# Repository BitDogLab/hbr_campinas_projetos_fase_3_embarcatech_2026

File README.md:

# EmbarcaTech 2026

## Repositório de Segurança - Projetos Finais da Fase 3

Este repositório contém cópias dos Projetos Finais dos alunos da 3ª Fase do Curso Embarcatech (1ª Edição, realizada de 10/2025 a 02/2025).

## Professores e Monitores
- Prof. Fabiano Fruett
- Prof. Lorenzo Coiado
- Rafael Camargo de Magalhães
- Timóteo Altoé Bento da Silva
- Vinícius Emanoel Ares

## Grupos

### G1 - Controle de Acesso
- Adriana Paula
- Bianca Andrade
  - *Saiu p/ Estágio em Empresa - 01/12/2025*
- Luana Menezes
> [!NOTE]
> Cópia de segurança não inclusa.

### G2 - Potência Óptica
- Elias Kento Tomiyama
- Felipe Leme
- Vinícius Caffeu
> [!NOTE]
> Cópia de segurança não inclusa.

### G3 - Chaveamento de Fibras Ópticas
- João Fernandes
- Paulo Filho

### G4 - Amigo Perto
- Antônio Almeida
- Eric Roma
- Vitor Souza

### G5 - Estação Meteorológica
- Antônio Crepaldi
- Carlos Perez
- Ricardo Jorge Furlan

### G6 - Ambientação
- Gabriel Mattano
- Jorge Wilker
- Roger Melo

### G7 - Robô
- Luan Azzi
- Vinícius Esperança Mantovani
  - *Saiu p/ Estágio em Empresa - 24/11/2025*
- Vagner Sanches Vasconcelos

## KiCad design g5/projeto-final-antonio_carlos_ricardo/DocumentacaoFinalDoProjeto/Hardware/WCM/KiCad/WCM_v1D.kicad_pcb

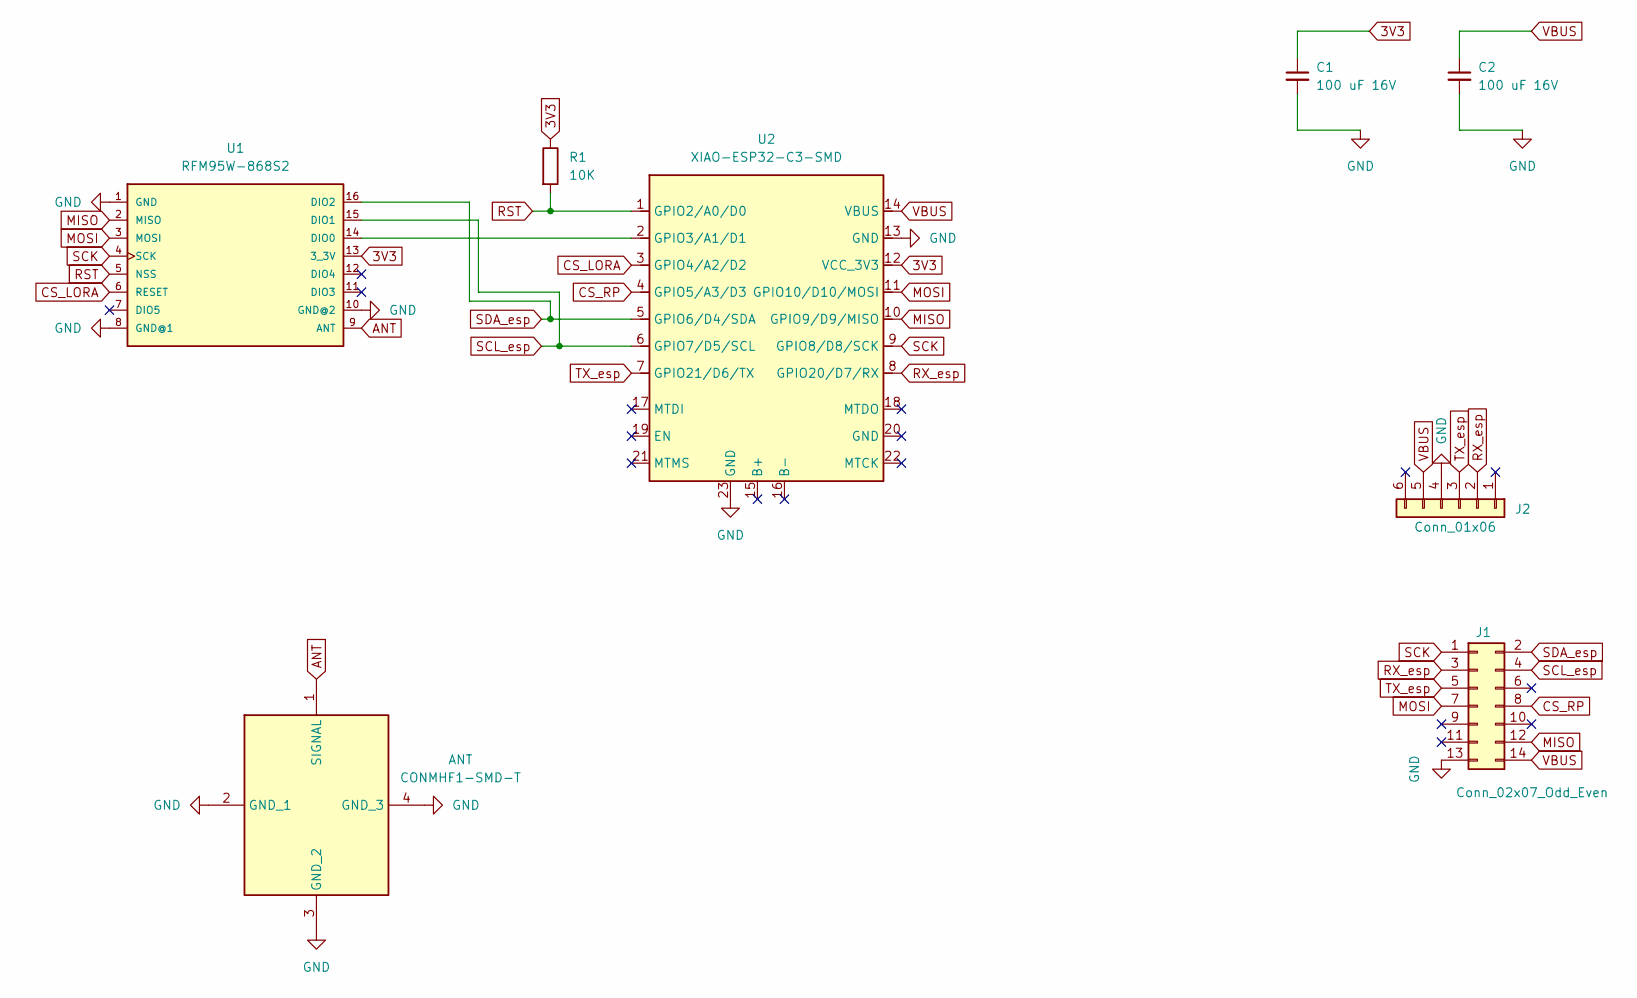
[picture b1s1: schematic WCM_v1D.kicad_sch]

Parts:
ANT: CONMHF1-SMD-T; CONMHF1SMDT; Mouser Part Number 712-CONMHF1-SMD-T
C1, C2: 100 uF 16V; CP_Elec_4x3.9
J1: Conn_02x07_Odd_Even; PinHeader_2x07_P2.54mm_Vertical_SMD
J2: Conn_01x06; PinHeader_1x06_P2.54mm_Vertical
R1: 10K; R_0603_1608Metric_Pad0.98x0.95mm_HandSolder
U1: RFM95W-868S2; XCVR_RFM95W-868S2
U2: XIAO-ESP32-C3-SMD; XIAO-ESP32C3-SMD

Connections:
3V3: C1.1, R1.1, U1.13 (3_3V), U2.12 (VCC_3V3)
ANT: ANT.1 (SIGNAL), U1.9 (ANT)
CS_LORA: U1.6 (RESET), U2.3 (GPIO4/A2/D2)
CS_RP: J1.8, U2.4 (GPIO5/A3/D3)
GND: ANT.2 (GND_1), ANT.3 (GND_2), ANT.4 (GND_3), C1.2, C2.2, J1.13, J2.4, U1.1 (GND), U1.8 (GND@1), U1.10 (GND@2), U2.13 (GND), U2.23 (GND)
MISO: J1.12, U1.2 (MISO), U2.10 (GPIO9/D9/MISO)
MOSI: J1.7, U1.3 (MOSI), U2.11 (GPIO10/D10/MOSI)
unnamed: U1.14 (DIO0), U2.2 (GPIO3/A1/D1)
RST: R1.2, U1.5 (NSS), U2.1 (GPIO2/A0/D0)
RX_esp: J1.3, J2.2, U2.8 (GPIO20/D7/RX)
SCK: J1.1, U1.4 (SCK), U2.9 (GPIO8/D8/SCK)
SCL_esp: J1.4, U1.15 (DIO1), U2.6 (GPIO7/D5/SCL)
SDA_esp: J1.2, U1.16 (DIO2), U2.5 (GPIO6/D4/SDA)
TX_esp: J1.5, J2.3, U2.7 (GPIO21/D6/TX)
VBUS: C2.1, J1.14, J2.5, U2.14 (VBUS)

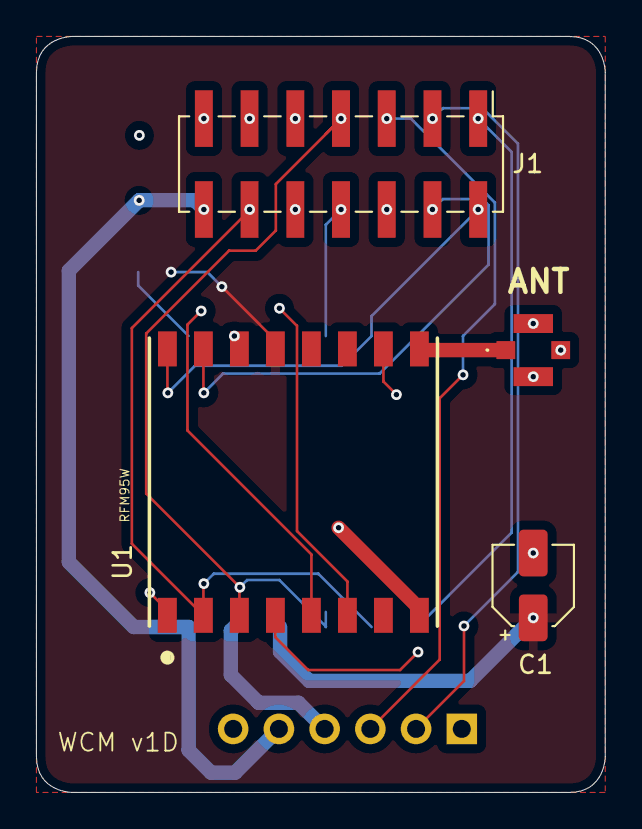
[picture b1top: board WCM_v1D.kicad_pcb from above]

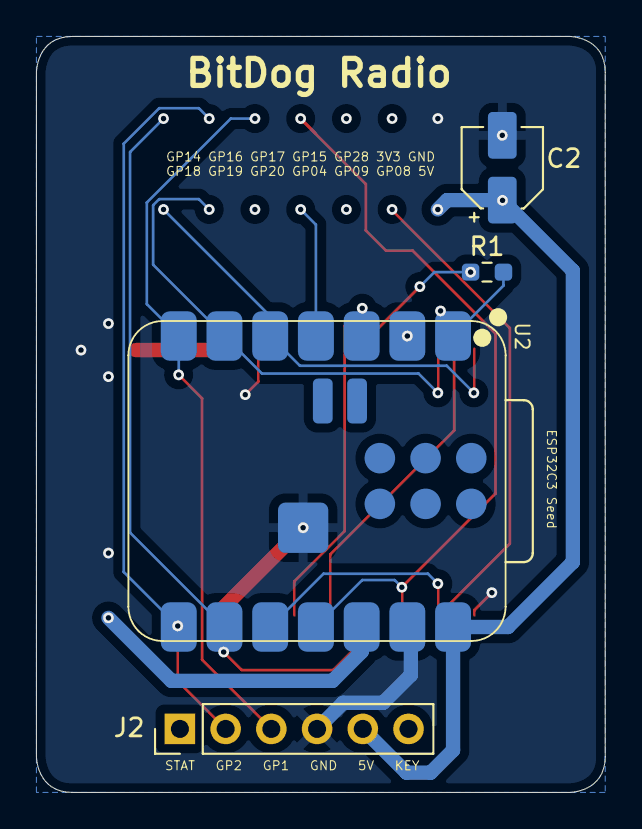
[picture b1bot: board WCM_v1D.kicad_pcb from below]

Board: 2 copper layers, 31.6 x 42.0 mm, 8 parts (4 on the bottom side), 15 nets.

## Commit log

2026-02-25 Add G3 files
2026-02-25 Fix folder
2026-02-25 Change folders' names
2026-02-25 Add folders
2026-02-25 Add presentation and documentation files
